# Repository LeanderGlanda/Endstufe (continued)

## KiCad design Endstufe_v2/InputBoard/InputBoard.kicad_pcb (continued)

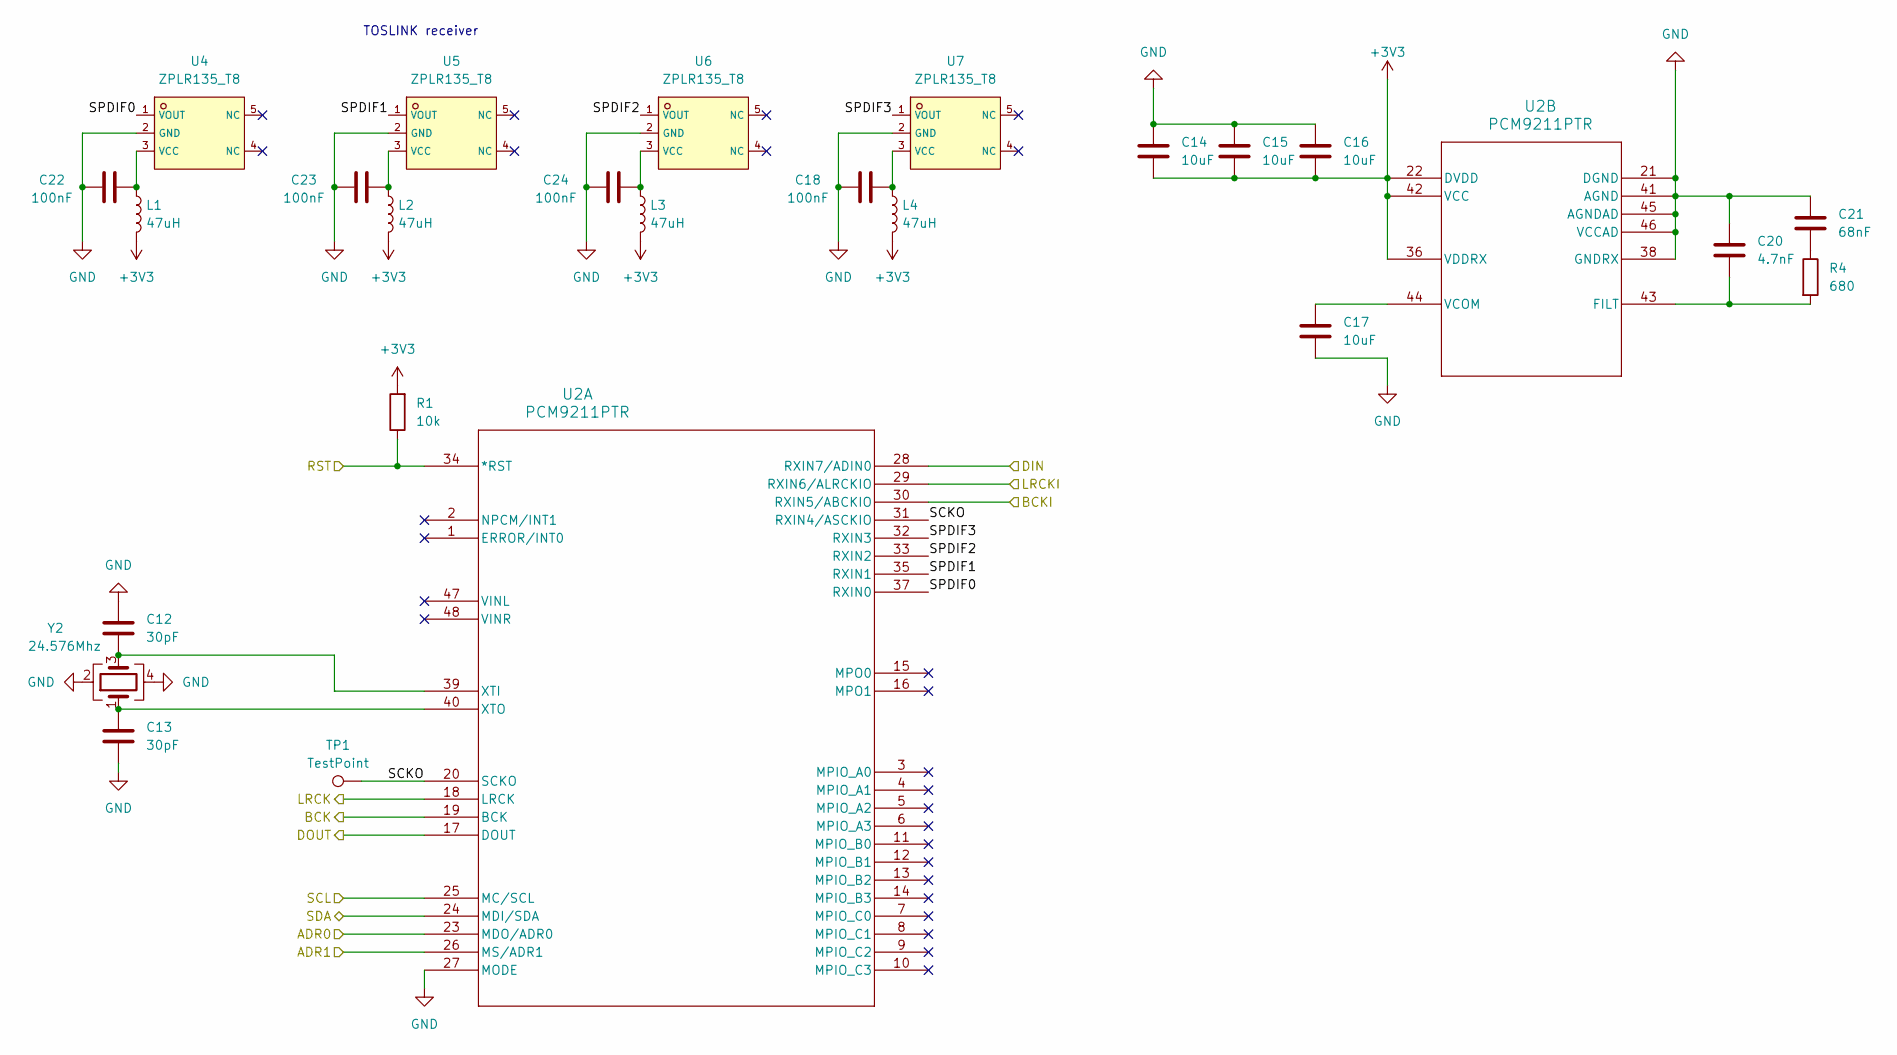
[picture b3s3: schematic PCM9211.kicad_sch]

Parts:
C12, C13: 30pF; C_0402_1005Metric; LCSC Part # C526980
C14, C15, C16, C17: 10uF; C_0402_1005Metric; LCSC Part # C15525
C18, C22, C23, C24: 100nF; C_0402_1005Metric; LCSC Part # C307331
C20: 4.7nF; C_0402_1005Metric; LCSC Part # C1518204
C21: 68nF; C_1206_3216Metric; LCSC Part # C77084
L1, L2, L3, L4: 47uH; L_0805_2012Metric; LCSC C383408
R1: 10k; R_0402_1005Metric; LCSC Part # C25744
R4: 680; R_0402_1005Metric; LCSC Part # C2684537
TP1: TestPoint; TestPoint_Pad_D1.0mm
U2: PCM9211PTR; TQFP-48_L7.0-W7.0-P0.50-LS9.0-TL; LCSC Part # C181660
U4, U5, U6, U7: ZPLR135_T8; CONN-TH_ZPLR135-T8; LCSC C277778
Y2: 24.576Mhz; OSC-SMD_4P-L3.2-W2.5-BL; LCSC Part # C2901683

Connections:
+3V3: C14.2, C15.2, C16.2, L1.2, L2.2, L3.2, L4.2, R1.2, U2.22 (DVDD), U2.36 (VDDRX), U2.42 (VCC); also elsewhere on the board
/PCM1865/SCL: U2.25 (MC/SCL); also elsewhere on the board
/PCM1865/SDA: U2.24 (MDI/SDA); also elsewhere on the board
/PCM9211/ADR0: U2.23 (MDO/ADR0); also elsewhere on the board
/PCM9211/ADR1: U2.26 (MS/ADR1); also elsewhere on the board
/PCM9211/BCK: U2.19 (BCK); also elsewhere on the board
/PCM9211/BCKI: U2.30 (RXIN5/ABCKIO); also elsewhere on the board
/PCM9211/DIN: U2.28 (RXIN7/ADIN0); also elsewhere on the board
/PCM9211/DOUT: U2.17 (DOUT); also elsewhere on the board
/PCM9211/LRCK: U2.18 (LRCK); also elsewhere on the board
/PCM9211/LRCKI: U2.29 (RXIN6/ALRCKIO); also elsewhere on the board
/PCM9211/RST: R1.1, U2.34 (*RST); also elsewhere on the board
/PCM9211/SCKO: TP1.1, U2.20 (SCKO), U2.31 (RXIN4/ASCKIO)
/PCM9211/SPDIF0: U2.37 (RXIN0), U4.1 (VOUT)
/PCM9211/SPDIF1: U2.35 (RXIN1), U5.1 (VOUT)
/PCM9211/SPDIF2: U2.33 (RXIN2), U6.1 (VOUT)
/PCM9211/SPDIF3: U2.32 (RXIN3), U7.1 (VOUT)
GND: C12.1, C13.2, C14.1, C15.1, C16.1, C17.2, C18.1, C20.2, C21.1, C22.1, C23.1, C24.1, U2.21 (DGND), U2.27 (MODE), U2.38 (GNDRX), U2.41 (AGND), U2.45 (AGNDAD), U2.46 (VCCAD), U4.2 (GND), U5.2 (GND), U6.2 (GND), U7.2 (GND), Y2.2, Y2.4; also elsewhere on the board
unnamed: C21.2, R4.1
unnamed: C12.2, U2.39 (XTI), Y2.3
unnamed: C13.1, U2.40 (XTO), Y2.1
unnamed: C20.1, R4.2, U2.43 (FILT)
unnamed: C17.1, U2.44 (VCOM)
unnamed: C22.2, L1.1, U4.3 (VCC)
unnamed: C23.2, L2.1, U5.3 (VCC)
unnamed: C24.2, L3.1, U6.3 (VCC)
unnamed: C18.2, L4.1, U7.3 (VCC)

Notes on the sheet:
TOSLINK receiver

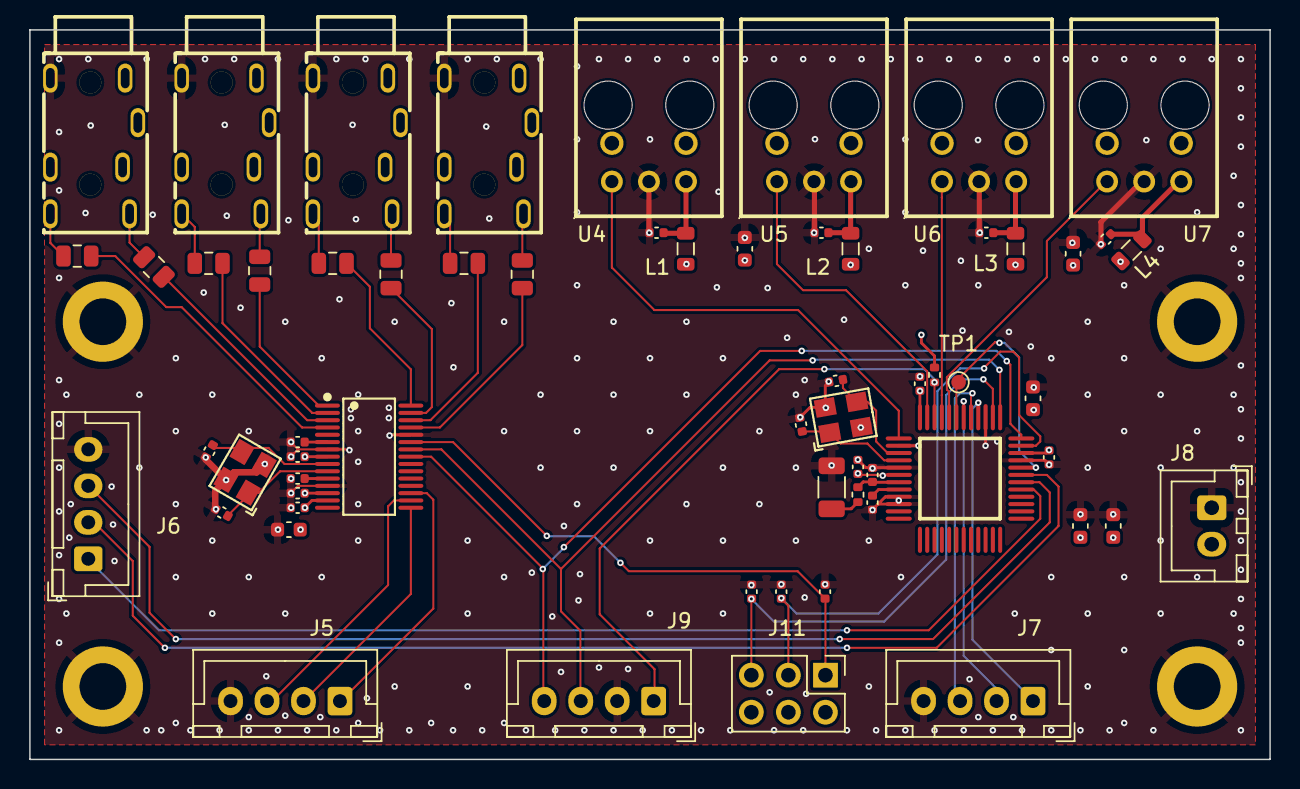
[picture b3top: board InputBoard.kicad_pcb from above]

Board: 4 copper layers, 85.0 x 50.0 mm, 65 parts (0 on the bottom side), 51 nets.

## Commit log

2024-02-03 Inital commit
2024-04-15 Completed first design
2024-04-25 Moved project into subfolder and update to KiCAD v8
2024-05-05 Add v2
2024-05-05 Add SigmaStudio trial project and libraries for ADAU1701 and S/PDIF connector
2024-05-18 Create 3 projects for 3 boards
2024-05-18 Upload code which was used for testing v1
2024-05-20 First touches on Control Board. This commit is for uploading the files.
2024-07-16 Fully connected ADAU1463
2024-07-16 Experiment with IO Settings in SigmaStudio
2024-07-28 Added ADAU1962A DAC schematic
2024-07-28 Remove temporary library files
2024-07-28 Ignore .lck files
2024-07-28 Add footprints to all components
2024-07-28 Fix connector footprints
2024-07-28 Rough layout of components
2024-07-29 Finish schematic of InputBoard and crate a rough layout
2024-08-06 Continue working on input board and use ADAU1467 instaed of ADAU1463
2024-08-06 Create schematic for amplifier board
2024-08-08 Layout amplifier board
2024-08-08 Continue layouting
2024-08-11 Make mounting holes and continue layouting
2024-08-13 Enlargen Amplifier Board to make space for mounting holes
2024-08-13 Finish layout of control and input board for now
2024-08-13 Add additional power connector to amplifier board
2024-08-13 Add forgotten 3V3 outputs to control board
2024-08-13 Add additional I2C headers
2024-08-13 Finalize layout and check DRC
2024-08-13 Select some design rules for PCB layouting
2024-08-15 Route input board
2024-08-17 Add resistor divider so 24V pull up can be connected to RP2040
2024-08-17 Route Power and Audio Signals
2024-08-17 Route TPA3126D2 output signals
2024-08-18 Finish routing of amplifier board
    Signals are now on layer 2, and layer 3 is 24V, layer 4 is GND.
    This makes the outer layers solid GND without many heat flow obstacles
2024-08-18 Route control board
2024-08-18 Routed DAC outputs
2024-08-18 Route control board (continued)
2024-08-18 Add missing I2C adress headers and pull down for DAC and DSP
2024-08-23 Routed all connections of control board
2024-08-23 Make PCB compliant with JLCPCB DFM tool
2024-08-24 Make footprints be stored in local library
2024-08-24 Fix more origins and rotations of footprints
2024-08-24 Change some component origins
2024-08-24 Fix origins and rotations of JST headers
2024-09-09 Move up SPDIF connectors
2024-09-09 Optimise placing of silkscreen
2024-09-09 Make boards compliant with JLCPCB
2024-09-09 Add information about I2C Addresses
2024-09-09 Fix selfboot not being activated
2024-09-09 Add panel for the three PCBs
2024-09-10 Change unavailable parts to available ones, optimise silkscreen, do via stiching
2024-09-10 Regenerate panels
2024-09-10 Regenerate panel
2024-09-29 Proof-of-concept code for DSP testing
2024-10-04 Reset panic to compensate for wrongly connected selfboot
2024-10-04 Work on PCM1865 and ADAU1962A
2024-10-06 First working software!
    There was an issue with DSP clocking it seems
2024-10-07 Try TDM4 for subwoofer output
2024-10-07 TDM4 not working
2024-10-07 Reverted to Stereo
2024-10-08 Change to TDM4
2024-10-11 Try SigmaStudio DAC control
2024-10-11 Correct SigmaStudio upload code
2024-10-11 Use ADAU1962A as I2S master
    Still doesn't work even though the signals look great on the
    oscilloscope
2024-10-12 Set sampling rate for ADAU1962A to 96kHz
    Now the signal gets transfered correctly... A high-pitched sound is
    noticeable but the analog input may be causing that. I guess so because
    unplugging the AUX cable makes the sound go away.
2024-10-12 Reactive subwoofer channel
    The 80Hz tone can be heared but there is a popping noise every second or
    so
2024-10-12 Use two I2S channels instead of TDM4
    This seems to work but there is a noise issue with the subwoofer
    channel, there is also some clicking happening on the other two
    channels. The fault is not the amplifier board, the noise can be listend
    to with headphones.
2024-10-12 Change back to 192kHz
    No improvements, but things didn't get worse either.
2024-10-12 Latch data on rising edge of ADAU1962A
    On the scope it looks like this is the correct option
2024-12-03 Change drive-strength and slew rate for SDATAIO
2024-12-05 Try using BCLK as clock source for DAC.
    The clocks of the DSP and the DAC should have the same source, but they
    do not. So using BCLK of the I2S as master clock source for the DAC
    could solve this issue. It did not work yet, as the PLL did not lock.
    These needs to be investigated further, maybe the DAC has to be powered
    down for a while?
2024-12-05 DAC works now :party:
    So the guy from Analog Devices was right: Different master clocks is the
    issue. In the last commit my temporary fix didn't work because I
    connected the BCLK from DSP to XTALO, but not MCLKI on the DAC. The
    audio sounds good right now, but a more long-term solution has to be
    found. Either it is possible to resolve the drifting clock issue in
    software (make the DSP reference the DAC) or a connection with a
2024-12-05 Use ASRC from DSP to avoid drifting clock issue
    The problem could be fixed in software.
2024-12-05 Some adjustments for audio output
    The PCM1865 signal now goes through an ASRC too, as in theory the clocks
    may also drift. A crossover for the subwoofer channel was also added
    with 3db gain, as the subwoofer has a lower SPL/1W than my other
    speakers. The TPA3116D2 amplifier ICs are still not noise-free, the
    power supply is probably not completely free noise. It couples into the
    audio path somehow. The noise is louder when I use my SMPS, and not as
2024-12-07 Make subwoofer channel 6dB louder than L/R
2024-12-07 Don't use ASRC for PCM1865 input
    It's not required and it makes the sound have clicks when resuming
    playback
2024-12-25 Add pretty register dump
2024-12-31 Change program to be used with ESP32
2025-01-07 Do not setup adau1962a
2025-01-24 Add i2c_slave lib
    It's necessary in the future so the ESP32 can send the RP2040
    information on which GPIOs to toggle
2025-01-24 Change subwoofer channel to be only +3dB louder
    It was +6dB previously
2025-01-25 Make the RP2040 an I2C slave which controls GPIOs
2025-01-25 Remove remaining pre-programmed GPIO control
    Every GPIO and all the system initialization is now done by ESP32
2025-01-30 Try changes for esp32 dsp input
2025-02-15 Input from ESP32 works now
2025-04-01 Most recent version of program
2025-05-05 Try something (extra headphone output I think)
2025-05-15 Current state: High pass filter for subwoofer, i2s stereo output + default logic
2025-05-15 Correct both crossovers to be the same
